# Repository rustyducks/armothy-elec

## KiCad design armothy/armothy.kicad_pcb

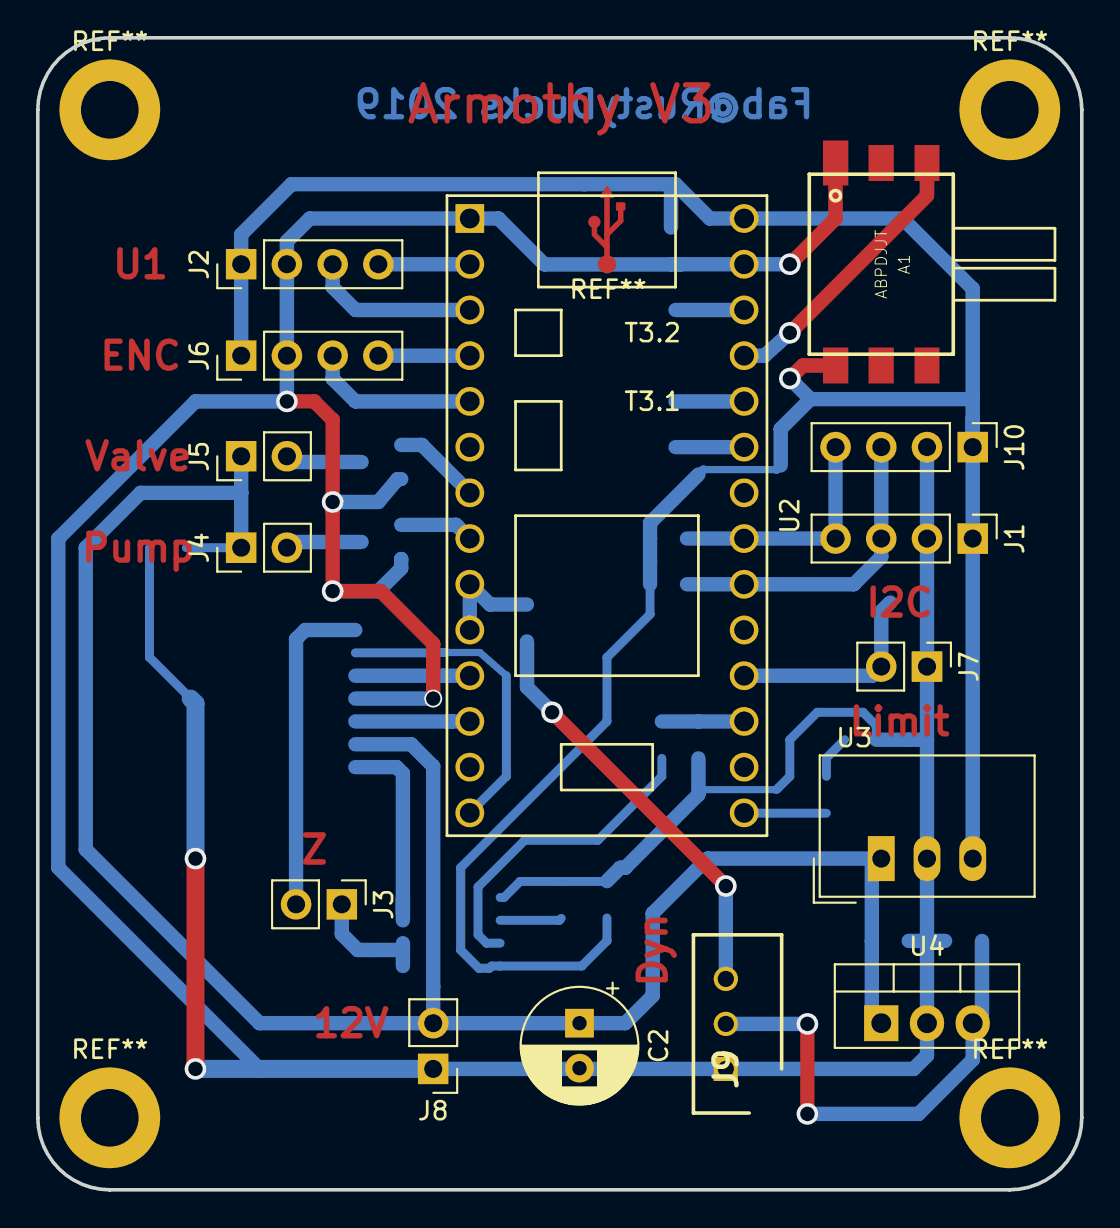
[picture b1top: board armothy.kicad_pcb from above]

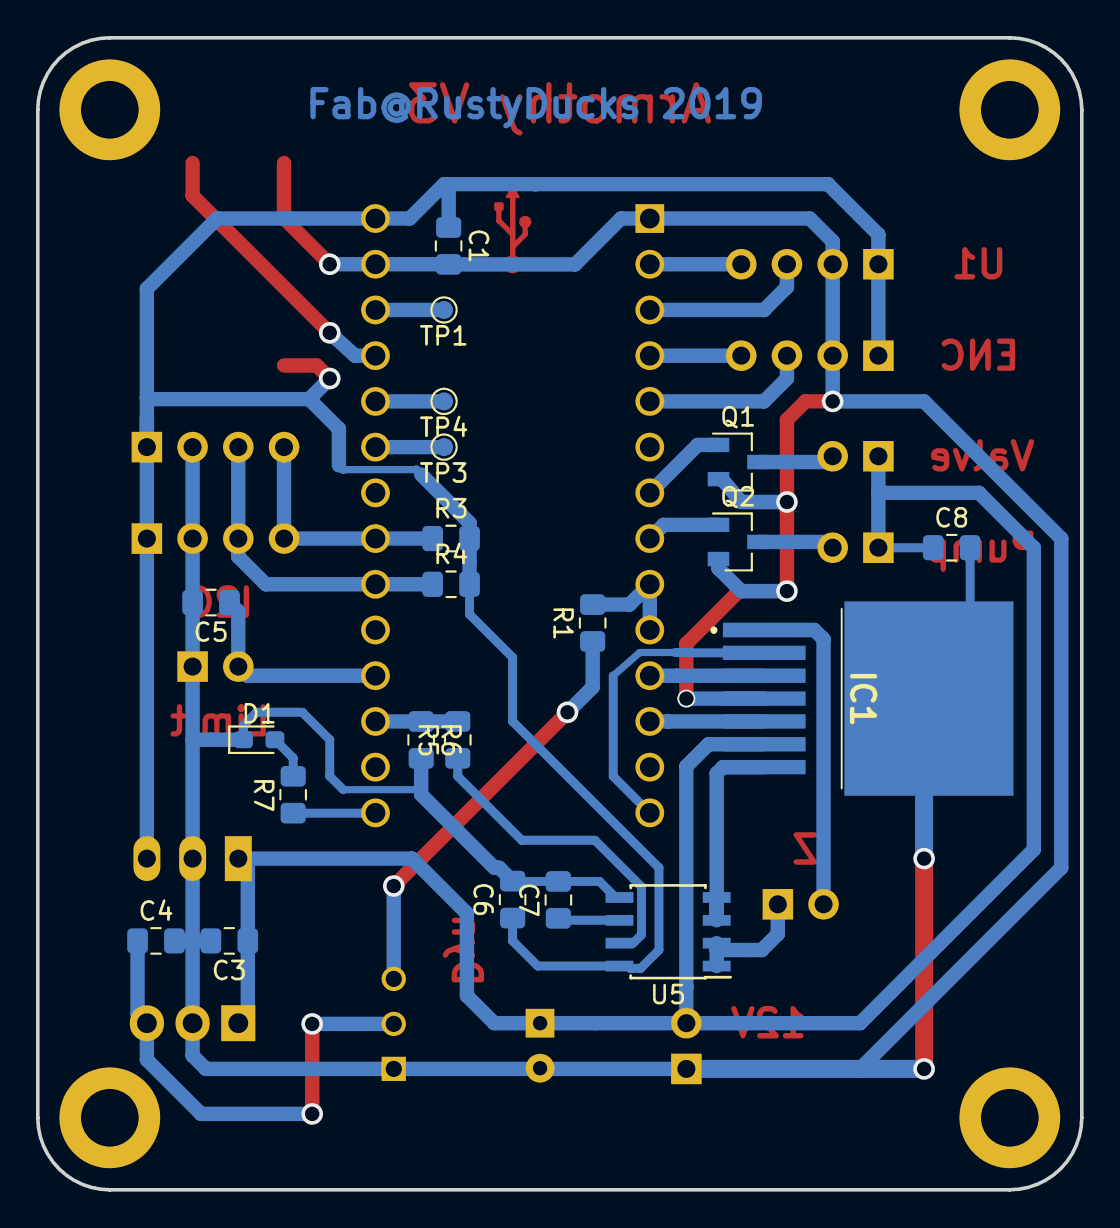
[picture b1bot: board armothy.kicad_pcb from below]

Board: 2 copper layers, 58.0 x 64.0 mm, 36 parts (21 on the bottom side), 32 nets.

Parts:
A1: ABPDJJT; DIP762W50P254L730H410Q6
C1, C4, C5, C6, C7, C8: 100n; C_0805_2012Metric_Pad1.15x1.40mm_HandSolder
C2: 100u; CP_Radial_D6.3mm_P2.50mm
C3: 330n; C_0805_2012Metric_Pad1.15x1.40mm_HandSolder
D1: LED; LED_0603_1608Metric_Pad1.05x0.95mm_HandSolder
IC1: TLE52052GAUMA1
J1, J10: I2C; PinHeader_1x04_P2.54mm_Vertical
J2: UART; PinHeader_1x04_P2.54mm_Vertical
J3: motZ; PinHeader_1x02_P2.54mm_Vertical
J4: pump; PinHeader_1x02_P2.54mm_Vertical
J5: valve; PinHeader_1x02_P2.54mm_Vertical
J6: Encoder; PinHeader_1x04_P2.54mm_Vertical
J7: Limit switch; PinHeader_1x02_P2.54mm_Vertical
J8: 12V_PWR; PinHeader_1x02_P2.54mm_Vertical
J9: Conn_01x03_Female; SHDR3W70P0X250_1X3_990X490X590P
Q1, Q2: IRL6283M; SOT-23
R1, R7: 100; R_0805_2012Metric_Pad1.15x1.40mm_HandSolder
R3, R4: 2.2K; R_0805_2012Metric_Pad1.15x1.40mm_HandSolder
R5: 5K; R_0805_2012Metric_Pad1.15x1.40mm_HandSolder
R6: 10K; R_0805_2012Metric_Pad1.15x1.40mm_HandSolder
TP1, TP3, TP4: TestPoint; TestPoint_Pad_D1.0mm
U2: Teensy3.2; Teensy30_31_32_LC
U3: TSR_1-2450; Converter_DCDC_TRACO_TSR-1_THT
U4: LM7810_TO220; TO-220-3_Vertical
U5: ACS712xLCTR-05B; SOIC-8_3.9x4.9mm_P1.27mm

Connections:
+5V: A1.6, C1.1, C6.1, J1.1, J2.1, J6.1, J10.1, R3.2, R4.2, U2.33, U3.3, U5.8
+10V: C4.1, J9.2, U4.3
+12V: C2.1, C3.1, C8.1, IC1.6, J4.1, J5.1, J8.2, U3.1, U4.1
/ENC_A: J6.3, U2.5
/ENC_B: J6.4, U2.4
/LIM_SWITCH: C5.1, J7.2, U2.23
/MOTORZ_A: IC1.5, U2.12
/MOTORZ_B: IC1.3, U2.11
/MOTORZ_EF: IC1.2, U2.14
/PRESSURE: A1.3, U2.30
/PUMP_CTRL: Q2.1, U2.8
/RX: J2.4, U2.2
/RX_DYN: R1.2, U2.9, U2.10
/SCL: J1.4, J10.4, R3.1, U2.26
/SDA: J1.3, J10.3, R4.1, U2.25
/STATUS_LED: R7.1, U2.20
/TX: J2.3, U2.3
/VALVE_CTRL: Q1.1, U2.7
/Z_CURRENT: R5.2, R6.1, U2.22
GND: A1.1, C1.2, C2.2, C3.2, C4.2, C5.2, C6.2, C7.2, C8.2, D1.1, IC1.4, IC1.8, J1.2, J2.2, J6.2, J7.1, J8.1, J9.1, J10.2, Q1.2, Q2.2, R6.2, U2.1, U2.32, U3.2, U4.2, U5.5
unnamed: C7.1, U5.6
unnamed: D1.2, R7.2
unnamed: IC1.1, J3.2
unnamed: IC1.7, U5.3, U5.4
unnamed: J3.1, U5.1, U5.2
unnamed: J4.2, Q2.3
unnamed: J5.2, Q1.3
unnamed: J9.3, R1.1
unnamed: R5.1, U5.7
unnamed: TP1.1, U2.31
unnamed: TP3.1, U2.28
unnamed: TP4.1, U2.29

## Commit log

2019-01-15 Adds pressure sensor
2019-01-15 Fixes encoder plug
2019-01-15 Changes 5V buck
2019-01-15 Adds interface (I2C, UART)
2019-02-05 Move libraries; improve schematic
2019-02-05 Adds .gitignore.
2019-02-06 Fix pin assignation; adds RGB led.
2019-02-06 Adds component numbers and page information.
2019-02-06 Remove submodule
2019-02-06 Adds teensy library out of submodule.
2019-02-08 Prototype version
2019-02-08 Improve libraries management; Adds Dynamixel connector 3D model (fix #4).
2019-02-08 Adds teensy 3D model (fix #3).
2019-02-08 Adds 3D models, fix ABPDJJT footprint (fix #1).
2019-02-15 Small improvement to schematic before the big ones.
2019-02-17 Armothy controller V2.0
2019-02-21 Changes LED footprint.
2022-02-04 latest changes
